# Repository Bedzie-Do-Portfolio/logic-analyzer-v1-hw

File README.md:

# logic-analyzer-v1-hw
Hardware for Logic Analyzer project
(Designed in KiCad)

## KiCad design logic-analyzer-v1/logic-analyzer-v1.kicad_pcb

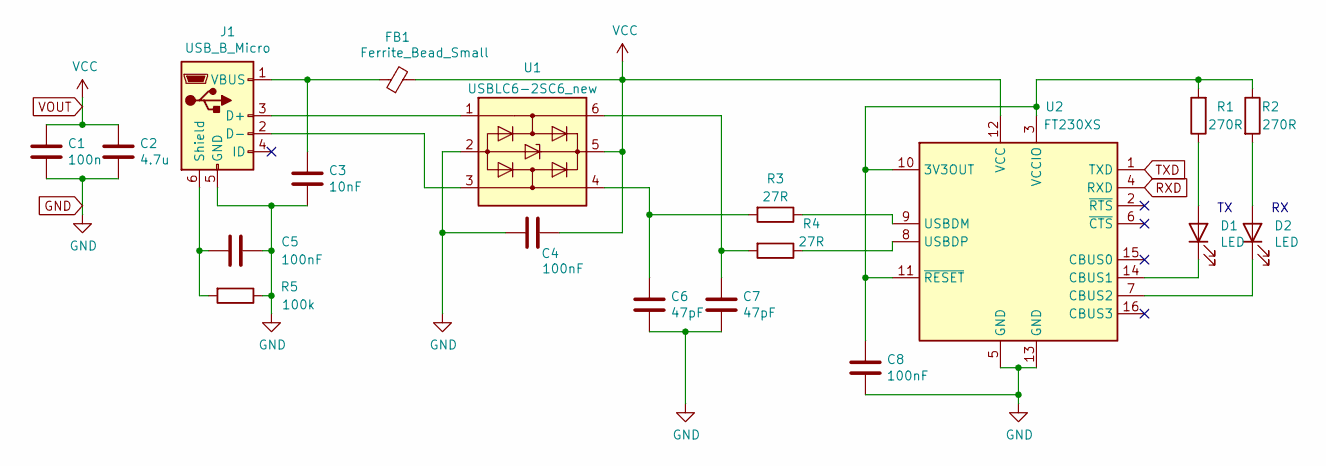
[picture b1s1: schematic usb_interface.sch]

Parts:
C1: 100n; C_0603_1608Metric_Pad1.05x0.95mm_HandSolder
C2: 4.7u; C_1206_3216Metric_Pad1.42x1.75mm_HandSolder
C3: 10nF; C_0603_1608Metric_Pad1.05x0.95mm_HandSolder
C4, C5, C8: 100nF; C_0603_1608Metric_Pad1.05x0.95mm_HandSolder
C6, C7: 47pF; C_0603_1608Metric_Pad1.05x0.95mm_HandSolder
D1, D2: LED; LED_0603_1608Metric_Pad1.05x0.95mm_HandSolder
FB1: Ferrite_Bead_Small; L_0603_1608Metric_Pad1.05x0.95mm_HandSolder
J1: USB_B_Micro; USB_Micro-B_Molex-105017-0001
R1, R2: 270R; R_0603_1608Metric_Pad1.05x0.95mm_HandSolder
R3, R4: 27R; R_0603_1608Metric_Pad1.05x0.95mm_HandSolder
R5: 100k; R_0603_1608Metric_Pad1.05x0.95mm_HandSolder
U1: USBLC6-2SC6_new; SOT-23-6
U2: FT230XS; SSOP-16_3.9x4.9mm_P0.635mm

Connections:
GND: C1.2, C2.2, C3.2, C4.2, C5.1, C6.2, C7.2, C8.2, J1.5 (GND), R5.1, U1.2 (GND), U2.5 (GND), U2.13 (GND)
unnamed: C3.1, FB1.1, J1.1 (VBUS)
unnamed: C5.2, J1.6 (Shield), R5.2
unnamed: C6.1, R3.2, U1.4 (I/O2)
unnamed: C7.1, R4.2, U1.6 (I/O1)
unnamed: C8.1, R1.2, R2.1, U2.3 (VCCIO), U2.10 (3V3OUT), U2.11 (~RESET)
unnamed: D1.1 (K), U2.14 (CBUS1)
unnamed: D1.2 (A), R1.1
unnamed: D2.1 (K), U2.7 (CBUS2)
unnamed: D2.2 (A), R2.2
unnamed: J1.2 (D-), U1.3 (I/O2)
unnamed: J1.3 (D+), U1.1 (I/O1)
unnamed: R3.1, U2.9 (USBDM)
unnamed: R4.1, U2.8 (USBDP)
RXD: U2.4 (RXD)
TXD: U2.1 (TXD)
VOUT: C1.1, C2.1, C4.1, FB1.2, U1.5 (VBUS), U2.12 (VCC)

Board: 2 copper layers, 19 parts (0 on the bottom side), 15 nets, no tracks yet.

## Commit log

2020-07-10 Add inint project, usb interface
2020-07-10 MOD usb-interface - review and minor fixes
2020-08-21 modify mcu sheet -> adding front end
2020-08-22 MOD usb power nets fix, mcu fixes
2020-08-22 adding gpio pins, usb pins, usart pins
2020-08-22 adding mod spi
2020-08-24 adding 2x spi memory
2021-04-11 add comparator&sram
2021-04-25 ADD shmitt_trigger.sch interface
2021-04-25 MOD uart port direction, minor cosmetic changes
2021-04-25 improvement origin in libraries and creation my_library containing all ours libraries
2021-05-03 changing sram blocks from new library
